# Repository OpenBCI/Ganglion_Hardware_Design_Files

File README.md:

# Ganglion_Hardware_Design_Files
General repo for Ganglion hardware files 

All design files made with KiCad PCB design software.
http://kicad.org/

Disclaimer:

These files are presented AS IS, with no representation of warranty or functionality.
Designs are subject to change without notice.

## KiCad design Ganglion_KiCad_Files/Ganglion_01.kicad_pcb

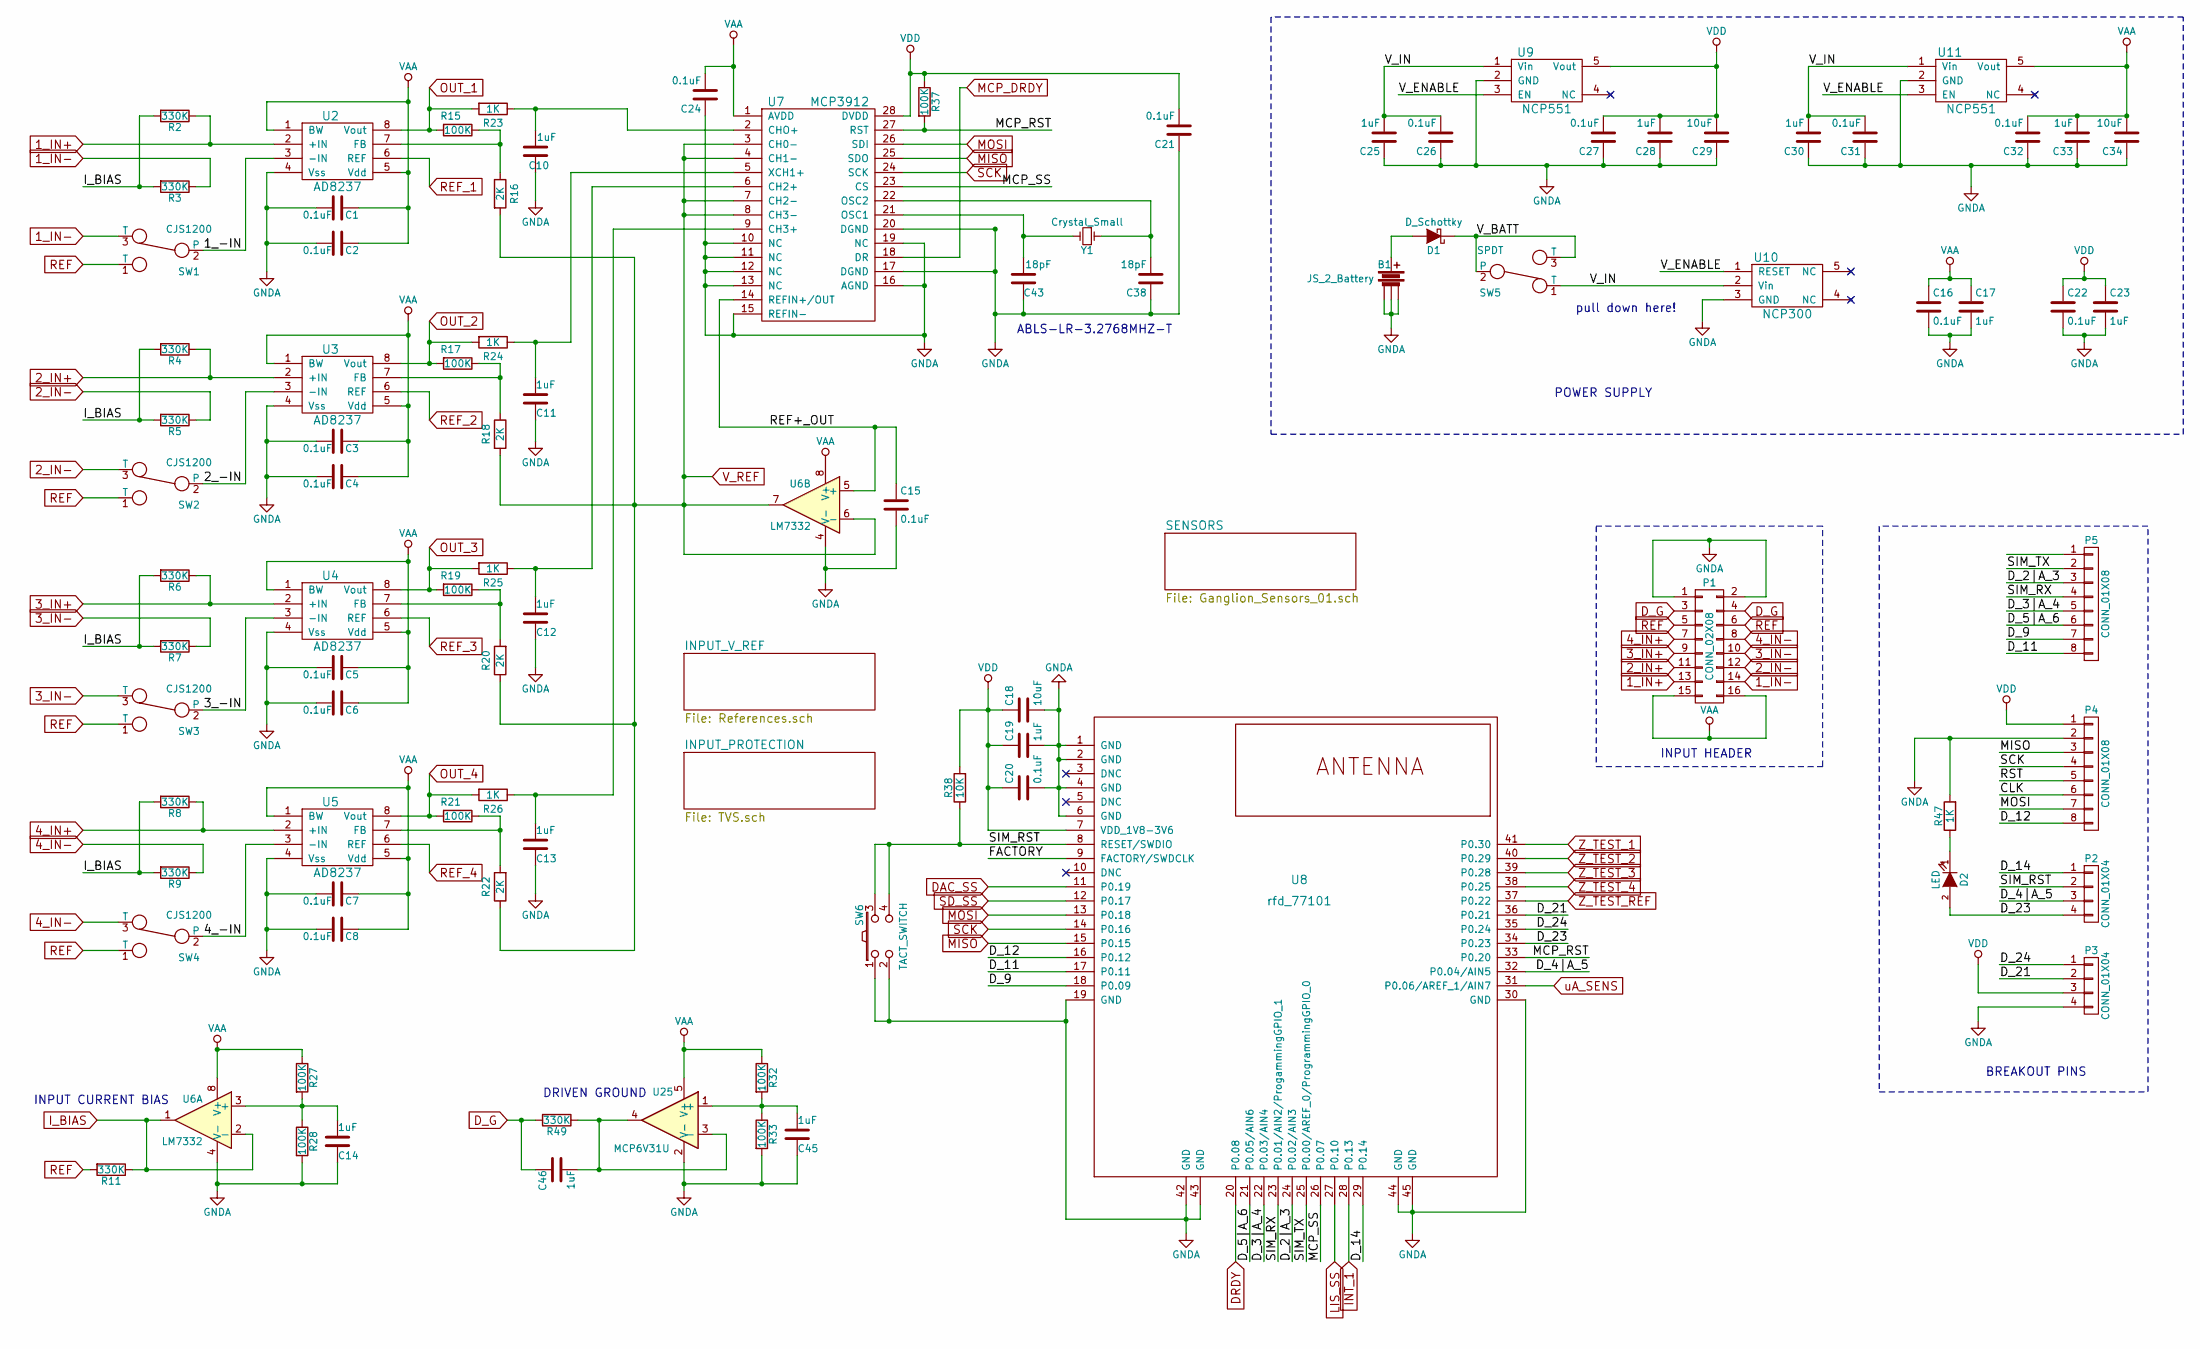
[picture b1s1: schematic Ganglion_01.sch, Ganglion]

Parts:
B1: JS_2_Battery; JST_RA_SMT; ManufacturerPartNumber S2B-PH-SM4-TB(LF)(SN)
C1, C2, C3, C4, C5, C6, C7, C8, C15, C16, C20, C21, C22, C24, C26, C27, C31, C32: 0.1uF; C_0603; ManufacturerPartNumber GRM188R71H104KA93D
C10, C11, C12, C13, C14, C17, C19, C23, C25, C28, C30, C33, C45: 1uF; C_0603; ManufacturerPartNumber GRM188R61E105KA12D
C18, C29, C34: 10uF; C_0603; ManufacturerPartNumber GRM188C80G106ME47D
C38, C43: 18pF; C_0603; ManufacturerPartNumber GRM1885C1H180JA01D
C46: 1uF; C_0603; ManufacturerPartNumber GRM188R71H104KA93D
D1: D_Schottky; C_0603; ManufacturerPartNumber CDBU0130L
D2: LED; LED_0603; ManufacturerPartNumber LTST-C193TBKT-5A
P1: CONN_02X08; Pin_Header_Angled_2x08; ManufacturerPartNumber PRPC008DBAN-M71RC
P2, P3: CONN_01X04; Socket_Strip_Straight_1x04; ManufacturerPartNumber PPTC041LFBN-RC
P4, P5: CONN_01X08; Socket_Strip_Straight_1x08; ManufacturerPartNumber PPTC081LFBN-RC
R2, R3, R4, R5, R6, R7, R8, R9, R11, R49: 330K; R_0603; ManufacturerPartNumber ERJ-3EKF3303V
R15, R17, R19, R21, R27, R28, R32, R33, R37: 100K; R_0603; ManufacturerPartNumber ERJ-3EKF1003V
R16, R18, R20, R22: 2K; R_0603; ManufacturerPartNumber ERJ-3EKF2001V
R23, R24, R25, R26, R47: 1K; R_0603; ManufacturerPartNumber ERJ-3EKF1001V
R38: 10K; R_0603; ManufacturerPartNumber ERJ-3EKF1002V
SW1, SW2, SW3, SW4: CJS1200; CJS-1200TA; ManufacturerPartNumber CJS-1200TA
SW5: SPDT; SSSS810701 SSSS810701; ManufacturerPartNumber SSSS810701
SW6: TACT_SWITCH; PTS810; ManufacturerPartNumber PTS810 SJK 250 SMTR LFS
U2, U3, U4, U5: AD8237; MSOP-8_3x3mm_Pitch0.65mm; ManufacturerPartNumber AD8237ARMZ-R7
U6: LM7332; MSOP-8_3x3mm_Pitch0.65mm; ManufacturerPartNumber MCP6L02T-E/MS
U7: MCP3912; SSOP-28_5.3x10.2mm_Pitch0.65mm; ManufacturerPartNumber MCP3912A1-E/SS
U8: rfd_77101; RFD77101; ManufacturerPartNumber RFD77101
U9, U11: NCP551; SOT-23-5; ManufacturerPartNumber NCP551SN30T1G
U10: NCP300; SOT-23-5; ManufacturerPartNumber NCP300LSN30T1G
U25: MCP6V31U; SC-70-5; ManufacturerPartNumber MCP6V31UT-E/LT
Y1: Crystal_Small; Crystal_HC49-SD_SMD; ManufacturerPartNumber ABLS-LR-3.2768MHZ-T

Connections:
1_IN+: P1.13, R2.1, U2.2 (+IN); also elsewhere on the board
1_IN-: P1.14, R3.1, SW1.3 (T); also elsewhere on the board
2_IN+: P1.11, R4.1, U3.2 (+IN); also elsewhere on the board
2_IN-: P1.12, R5.1, SW2.3 (T); also elsewhere on the board
3_IN+: P1.9, R6.1, U4.2 (+IN); also elsewhere on the board
3_IN-: P1.10, R7.1, SW3.3 (T); also elsewhere on the board
4_IN+: P1.7, R8.1, U5.2 (+IN); also elsewhere on the board
4_IN-: P1.8, R9.1, SW4.3 (T); also elsewhere on the board
/1_-IN: SW1.2, U2.3 (-IN)
/2_-IN: SW2.2, U3.3 (-IN)
/3_-IN: SW3.2, U4.3 (-IN)
/4_-IN: SW4.2, U5.3 (-IN)
/CLK: P4.6
/D_2|A_3: P5.3, U8.24 (P0.02/AIN3)
/D_3|A_4: P5.5, U8.22 (P0.03/AIN4)
/D_4|A_5: P2.3, U8.32 (P0.04/AIN5)
/D_5|A_6: P5.6, U8.21 (P0.05/AIN6)
/D_9: P5.7, U8.18 (P0.09)
/D_11: P5.8, U8.17 (P0.11)
/D_12: P4.8, U8.16 (P0.12)
/D_14: P2.1, U8.29 (P0.14)
/D_21: P3.2, U8.36 (P0.21)
/D_23: D2.2 (A), P2.4, U8.34 (P0.23)
/D_24: P3.1, U8.35 (P0.24)
/FACTORY: U8.9 (FACTORY/SWDCLK)
/MCP_RST: R37.2, U7.27 (RST), U8.33 (P0.20)
/MCP_SS: U7.23 (CS), U8.26 (P0.07)
/REF+_OUT: C15.1, U6.5 (+), U7.14 (REFIN+/OUT)
/RST: P4.5
/SIM_RST: P2.2, R38.1, SW6.3, SW6.4, U8.8 (RESET/SWDIO)
/SIM_RX: P5.4, U8.23 (P0.01/AIN2/ProgammingGPIO_1)
/SIM_TX: P5.2, U8.25 (P0.00/AREF_0/ProgrammingGPIO_0)
/V_BATT: D1.1 (K), SW5.2, SW5.3 (T)
/V_ENABLE: U9.3 (EN), U10.1 (RESET), U11.3 (EN)
/V_IN: C25.2, C26.2, C30.2, C31.2, SW5.1 (T), U9.1 (Vin), U10.2 (Vin), U11.1 (Vin)
DAC_SS: U8.11 (P0.19); also elsewhere on the board
DRDY: U8.20 (P0.08); also elsewhere on the board
D_G: C46.2, P1.3, P1.4, R49.2; also elsewhere on the board
GNDA: B1.2, B1.3, B1.4, C1.2, C2.2, C3.2, C4.2, C5.2, C6.2, C7.2, C8.2, C10.1, C11.2, C12.2, C13.2, C14.2, C15.2, C16.2, C17.2, C18.2, C19.2, C20.2, C21.1, C22.2, C23.2, C24.1, C25.1, C26.1, C27.1, C28.1, C29.1, C30.1, C31.1, C32.1, C33.1, C34.1, C38.1, C43.1, C45.2, P1.1, P1.2, P3.4, P4.2, R28.2, R33.2, R47.2, SW6.1, SW6.2, U2.4 (Vss), U3.4 (Vss), U4.4 (Vss), U5.4 (Vss), U6.4 (V-), U7.10 (NC), U7.11 (NC), U7.12 (NC), U7.13 (NC), U7.15 (REFIN-), U7.16 (AGND), U7.17 (DGND), U7.19 (NC), U7.20 (DGND), U8.1 (GND), U8.2 (GND), U8.4 (GND), U8.6 (GND), U8.19 (GND), U8.30 (GND), U8.42 (GND), U8.43 (GND), U8.44 (GND), U8.45 (GND), U9.2 (GND), U10.3 (GND), U11.2 (GND), U25.2 (V-); also elsewhere on the board
INT_1: U8.28 (P0.13); also elsewhere on the board
I_BIAS: R2.2, R3.2, R4.2, R5.2, R6.2, R7.2, R8.2, R9.2, R11.1, U6.1, U6.2 (-)
LIS_SS: U8.27 (P0.10); also elsewhere on the board
MCP_DRDY: U7.18 (DR); also elsewhere on the board
MISO: P4.3, U7.25 (SDO), U8.15 (P0.15); also elsewhere on the board
MOSI: P4.7, U7.26 (SDI), U8.13 (P0.18); also elsewhere on the board
unnamed: B1.1, D1.2 (A)
unnamed: C10.2, R23.1, U7.2 (CHO+)
unnamed: C11.1, R24.1, U7.5 (XCH1+)
unnamed: C12.1, R25.1, U7.6 (CH2+)
unnamed: C13.1, R26.1, U7.9 (CH3+)
unnamed: C14.1, R27.2, R28.1, U6.3 (+)
unnamed: C38.2, U7.22 (OSC2), Y1.1
unnamed: C43.2, U7.21 (OSC1), Y1.2
unnamed: C45.1, R32.2, R33.1, U25.1 (+)
unnamed: C46.1, R49.1, U25.3 (-), U25.4
unnamed: D2.1 (K), R47.1
unnamed: R15.1, R16.1, U2.7 (FB)
unnamed: R17.1, R18.1, U3.7 (FB)
unnamed: R19.1, R20.2, U4.7 (FB)
unnamed: R21.1, R22.2, U5.7 (FB)
OUT_1: R15.2, R23.2, U2.8 (Vout); also elsewhere on the board
OUT_2: R17.2, R24.2, U3.8 (Vout); also elsewhere on the board
OUT_3: R19.2, R25.2, U4.8 (Vout); also elsewhere on the board
OUT_4: R21.2, R26.2, U5.8 (Vout); also elsewhere on the board
REF: P1.5, P1.6, R11.2, SW1.1 (T), SW2.1 (T), SW3.1 (T), SW4.1 (T); also elsewhere on the board
REF_1: U2.6 (REF); also elsewhere on the board
REF_2: U3.6 (REF); also elsewhere on the board
REF_3: U4.6 (REF); also elsewhere on the board
REF_4: U5.6 (REF); also elsewhere on the board
SCK: P4.4, U7.24 (SCK), U8.14 (P0.16); also elsewhere on the board
SD_SS: U8.12 (P0.17); also elsewhere on the board
VAA: C1.1, C2.1, C3.1, C4.1, C5.1, C6.1, C7.1, C8.1, C16.1, C17.1, C24.2, C32.2, C33.2, C34.2, P1.15, P1.16, R27.1, R32.1, U2.1 (BW), U2.5 (Vdd), U3.1 (BW), U3.5 (Vdd), U4.1 (BW), U4.5 (Vdd), U5.1 (BW), U5.5 (Vdd), U6.8 (V+), U7.1 (AVDD), U11.5 (Vout), U25.5 (V+); also elsewhere on the board
VDD: C18.1, C19.1, C20.1, C21.2, C22.1, C23.1, C27.2, C28.2, C29.2, P3.3, P4.1, R37.1, R38.2, U7.28 (DVDD), U8.7 (VDD_1V8-3V6), U9.5 (Vout); also elsewhere on the board
V_REF: R16.2, R18.2, R20.1, R22.1, U6.6 (-), U6.7, U7.3 (CH0-), U7.4 (CH1-), U7.7 (CH2-), U7.8 (CH3-); also elsewhere on the board
Z_TEST_1: U8.41 (P0.30); also elsewhere on the board
Z_TEST_2: U8.40 (P0.29); also elsewhere on the board
Z_TEST_3: U8.39 (P0.28); also elsewhere on the board
Z_TEST_4: U8.38 (P0.25); also elsewhere on the board
Z_TEST_REF: U8.37 (P0.22); also elsewhere on the board
uA_SENS: U8.31 (P0.06/AREF_1/AIN7); also elsewhere on the board

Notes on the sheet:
POWER SUPPLY
BREAKOUT PINS
pull down here!
ABLS-LR-3.2768MHZ-T
DRIVEN GROUND
INPUT CURRENT BIAS
INPUT HEADER

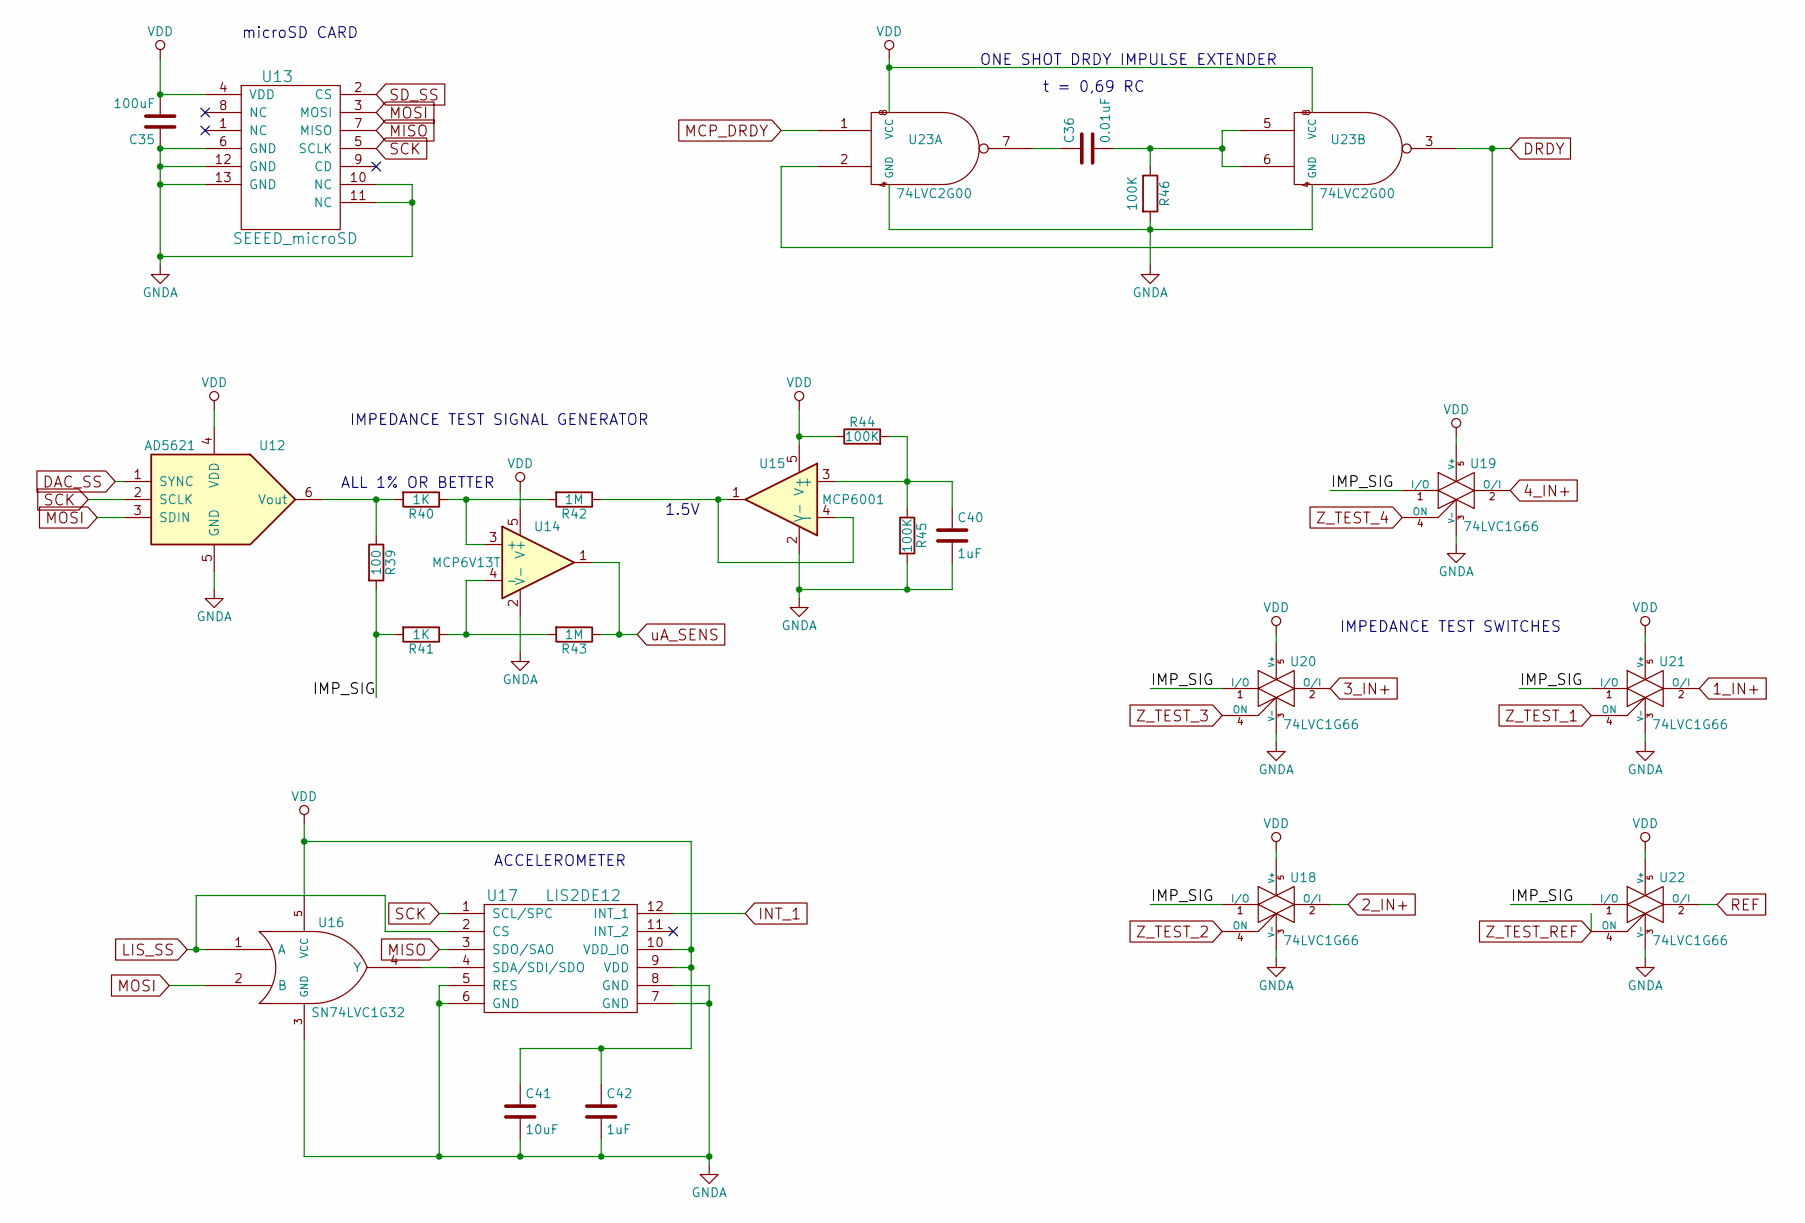
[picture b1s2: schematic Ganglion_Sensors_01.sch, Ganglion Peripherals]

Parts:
C35: 100uF; C_1210; ManufacturerPartNumber GRM21BR60J476ME15L
C36: 0.01uF; C_0603; ManufacturerPartNumber GCM188R71H103KA37D
C40, C42: 1uF; C_0603; ManufacturerPartNumber GRM188R61E105KA12D
C41: 10uF; C_0603; ManufacturerPartNumber GRM188C80G106ME47D
R39: 100; R_0603; ManufacturerPartNumber ERJ-3EKF1000V
R40, R41: 1K; R_0603; ManufacturerPartNumber ERJ-3EKF1001V
R42, R43: 1M; R_0603; ManufacturerPartNumber ERJ-3EKF1004V
R44, R45, R46: 100K; R_0603; ManufacturerPartNumber ERJ-3EKF1003V
U12: AD5621; SC-70-6; ManufacturerPartNumber AD5621AKSZ-REEL7
U13: SEEED_microSD; ST-TF-0003A; ManufacturerPartNumber ST-TF-003A
U14: MCP6V13T; SOT-23-5; ManufacturerPartNumber MCP6V31T-E/OT
U15: MCP6001; SC-70-5; ManufacturerPartNumber MCP6001T-I/LT
U16: SN74LVC1G32; SC-70-5; ManufacturerPartNumber SN74LVC1G32DCKR
U17: LIS2DE12; LIS2DH12; ManufacturerPartNumber LIS2DE12TR
U18, U19, U20, U21, U22: 74LVC1G66; SC-70-5; ManufacturerPartNumber 74LVC1G66GW,125
U23: 74LVC2G00; VSSOP-8; ManufacturerPartNumber SN74LVC2G00DCUR

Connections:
1_IN+: U21.2 (O/I); also elsewhere on the board
2_IN+: U18.2 (O/I); also elsewhere on the board
3_IN+: U20.2 (O/I); also elsewhere on the board
4_IN+: U19.2 (O/I); also elsewhere on the board
/SENSORS/IMP_SIG: R39.2, R41.2, U18.1 (I/O), U19.1 (I/O), U20.1 (I/O), U21.1 (I/O), U22.1 (I/O)
DAC_SS: U12.1 (SYNC); also elsewhere on the board
DRDY: U23.2, U23.3; also elsewhere on the board
GNDA: C35.1, C40.2, C41.2, C42.2, R45.2, R46.2, U12.5 (GND), U13.6 (GND), U13.10 (NC), U13.11 (NC), U13.12 (GND), U13.13 (GND), U14.2 (V-), U15.2 (V-), U16.3 (GND), U17.5 (RES), U17.6 (GND), U17.7 (GND), U17.8 (GND), U18.3 (V-), U19.3 (V-), U20.3 (V-), U21.3 (V-), U22.3 (V-), U23.4 (GND); also elsewhere on the board
INT_1: U17.12 (INT_1); also elsewhere on the board
LIS_SS: U16.1 (A), U17.2 (CS); also elsewhere on the board
MCP_DRDY: U23.1; also elsewhere on the board
MISO: U13.7 (MISO), U17.3 (SDO/SAO); also elsewhere on the board
MOSI: U12.3 (SDIN), U13.3 (MOSI), U16.2 (B); also elsewhere on the board
unnamed: C36.1, U23.7
unnamed: C36.2, R46.1, U23.5, U23.6
unnamed: C40.1, R44.2, R45.1, U15.3 (+)
unnamed: R39.1, R40.2, U12.6 (Vout)
unnamed: R40.1, R42.2, U14.3 (+)
unnamed: R41.1, R43.2, U14.4 (-)
unnamed: R42.1, U15.1, U15.4 (-)
unnamed: U16.4 (Y), U17.4 (SDA/SDI/SDO)
REF: U22.2 (O/I); also elsewhere on the board
SCK: U12.2 (SCLK), U13.5 (SCLK), U17.1 (SCL/SPC); also elsewhere on the board
SD_SS: U13.2 (CS); also elsewhere on the board
VDD: C35.2, C41.1, C42.1, R44.1, U12.4 (VDD), U13.4 (VDD), U14.5 (V+), U15.5 (V+), U16.5 (VCC), U17.9 (VDD), U17.10 (VDD_IO), U18.5 (V+), U19.5 (V+), U20.5 (V+), U21.5 (V+), U22.5 (V+), U23.8 (VCC); also elsewhere on the board
Z_TEST_1: U21.4 (ON); also elsewhere on the board
Z_TEST_2: U18.4 (ON); also elsewhere on the board
Z_TEST_3: U20.4 (ON); also elsewhere on the board
Z_TEST_4: U19.4 (ON); also elsewhere on the board
Z_TEST_REF: U22.4 (ON); also elsewhere on the board
uA_SENS: R43.1, U14.1; also elsewhere on the board

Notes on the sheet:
1.5V
ALL 1% OR BETTER
ACCELEROMETER
microSD CARD
IMPEDANCE TEST SIGNAL GENERATOR
ONE SHOT DRDY IMPULSE EXTENDER
t = 0,69 RC
IMPEDANCE TEST SWITCHES

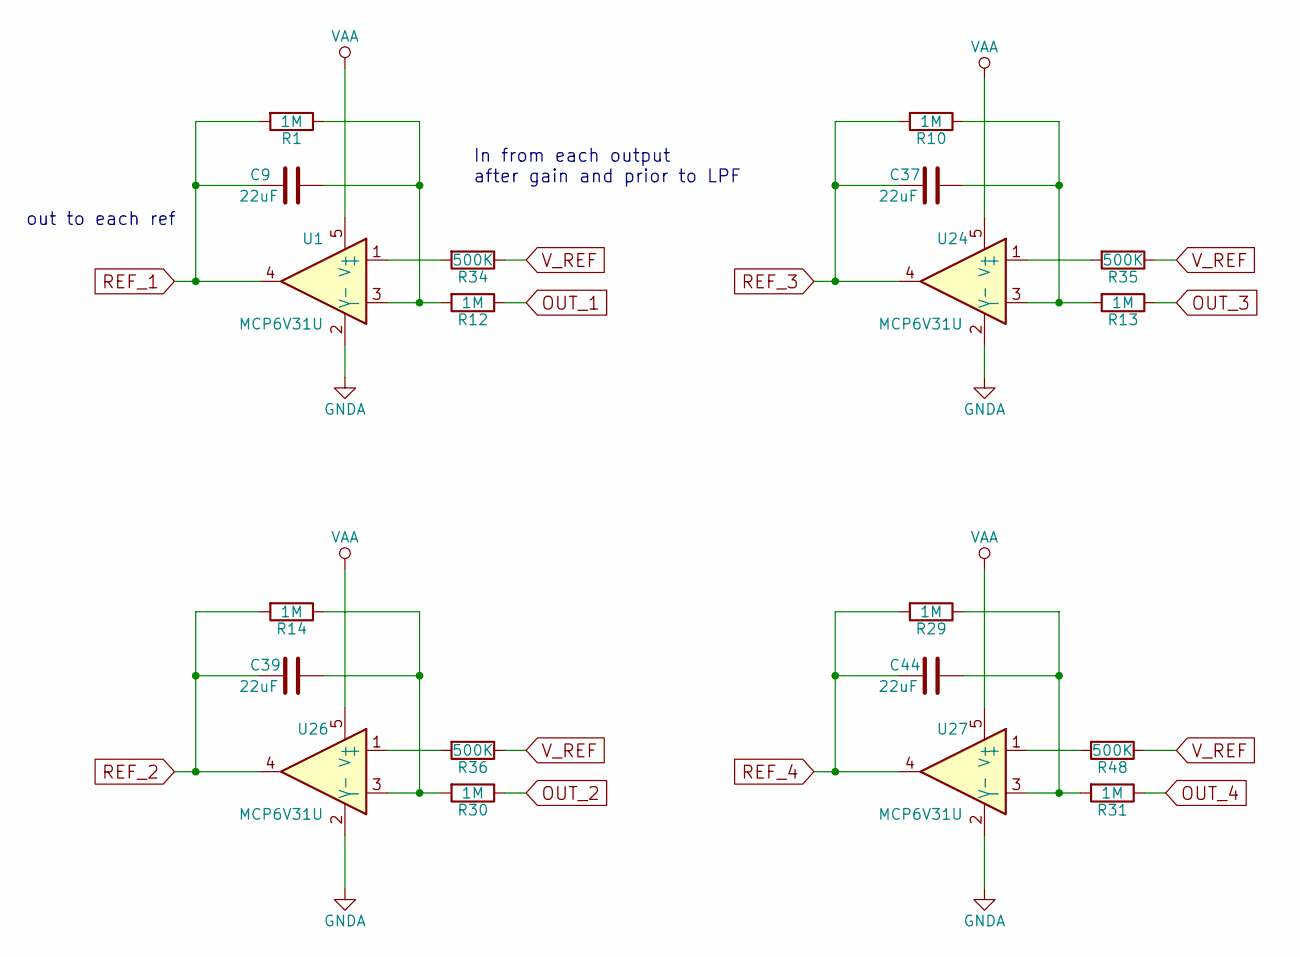
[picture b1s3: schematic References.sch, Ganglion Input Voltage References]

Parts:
C9, C37, C39, C44: 22uF; C_0603; ManufacturerPartNumber GRM188R60J226MEA0D
R1, R10, R12, R13, R14, R29, R30, R31: 1M; C_0603; ManufacturerPartNumber ERJ-3EKF1004V
R34, R35, R36, R48: 500K; C_0603; ManufacturerPartNumber CR0603-FX-4993ELF
U1, U24, U26, U27: MCP6V31U; SC-70-5; ManufacturerPartNumber MCP6V31UT-E/LT

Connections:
GNDA: U1.2 (V-), U24.2 (V-), U26.2 (V-), U27.2 (V-); also elsewhere on the board
unnamed: C9.1, R1.1, R12.2, U1.3 (-)
unnamed: C37.1, R10.1, R13.2, U24.3 (-)
unnamed: C39.1, R14.1, R30.2, U26.3 (-)
unnamed: C44.1, R29.1, R31.2, U27.3 (-)
unnamed: R34.2, U1.1 (+)
unnamed: R35.2, U24.1 (+)
unnamed: R36.2, U26.1 (+)
unnamed: R48.2, U27.1 (+)
OUT_1: R12.1; also elsewhere on the board
OUT_2: R30.1; also elsewhere on the board
OUT_3: R13.1; also elsewhere on the board
OUT_4: R31.1; also elsewhere on the board
REF_1: C9.2, R1.2, U1.4; also elsewhere on the board
REF_2: C39.2, R14.2, U26.4; also elsewhere on the board
REF_3: C37.2, R10.2, U24.4; also elsewhere on the board
REF_4: C44.2, R29.2, U27.4; also elsewhere on the board
VAA: U1.5 (V+), U24.5 (V+), U26.5 (V+), U27.5 (V+); also elsewhere on the board
V_REF: R34.1, R35.1, R36.1, R48.1; also elsewhere on the board

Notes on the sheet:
In from each output after gain and prior to LPF
out to each ref

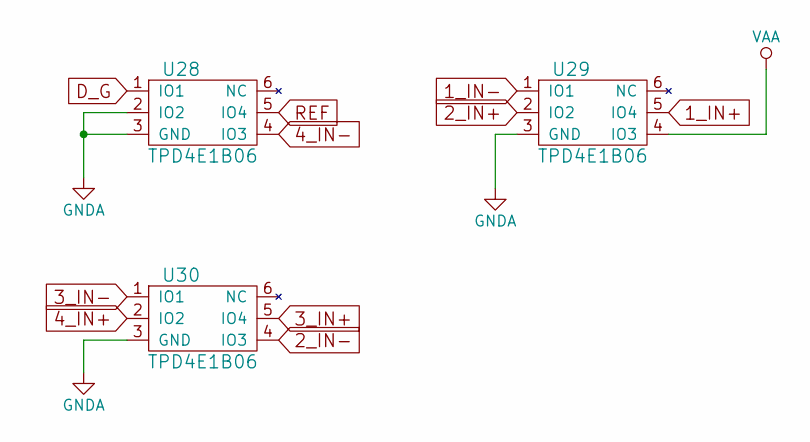
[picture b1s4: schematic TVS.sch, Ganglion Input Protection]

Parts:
U28, U29, U30: TPD4E1B06; SC-70-6; ManufacturerPartNumber TPD4E1B06DCKR

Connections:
1_IN+: U29.5 (IO4); also elsewhere on the board
1_IN-: U29.1 (IO1); also elsewhere on the board
2_IN+: U29.2 (IO2); also elsewhere on the board
2_IN-: U30.4 (IO3); also elsewhere on the board
3_IN+: U30.5 (IO4); also elsewhere on the board
3_IN-: U30.1 (IO1); also elsewhere on the board
4_IN+: U30.2 (IO2); also elsewhere on the board
4_IN-: U28.4 (IO3); also elsewhere on the board
D_G: U28.1 (IO1); also elsewhere on the board
GNDA: U28.2 (IO2), U28.3 (GND), U29.3 (GND), U30.3 (GND); also elsewhere on the board
REF: U28.5 (IO4); also elsewhere on the board
VAA: U29.4 (IO3); also elsewhere on the board

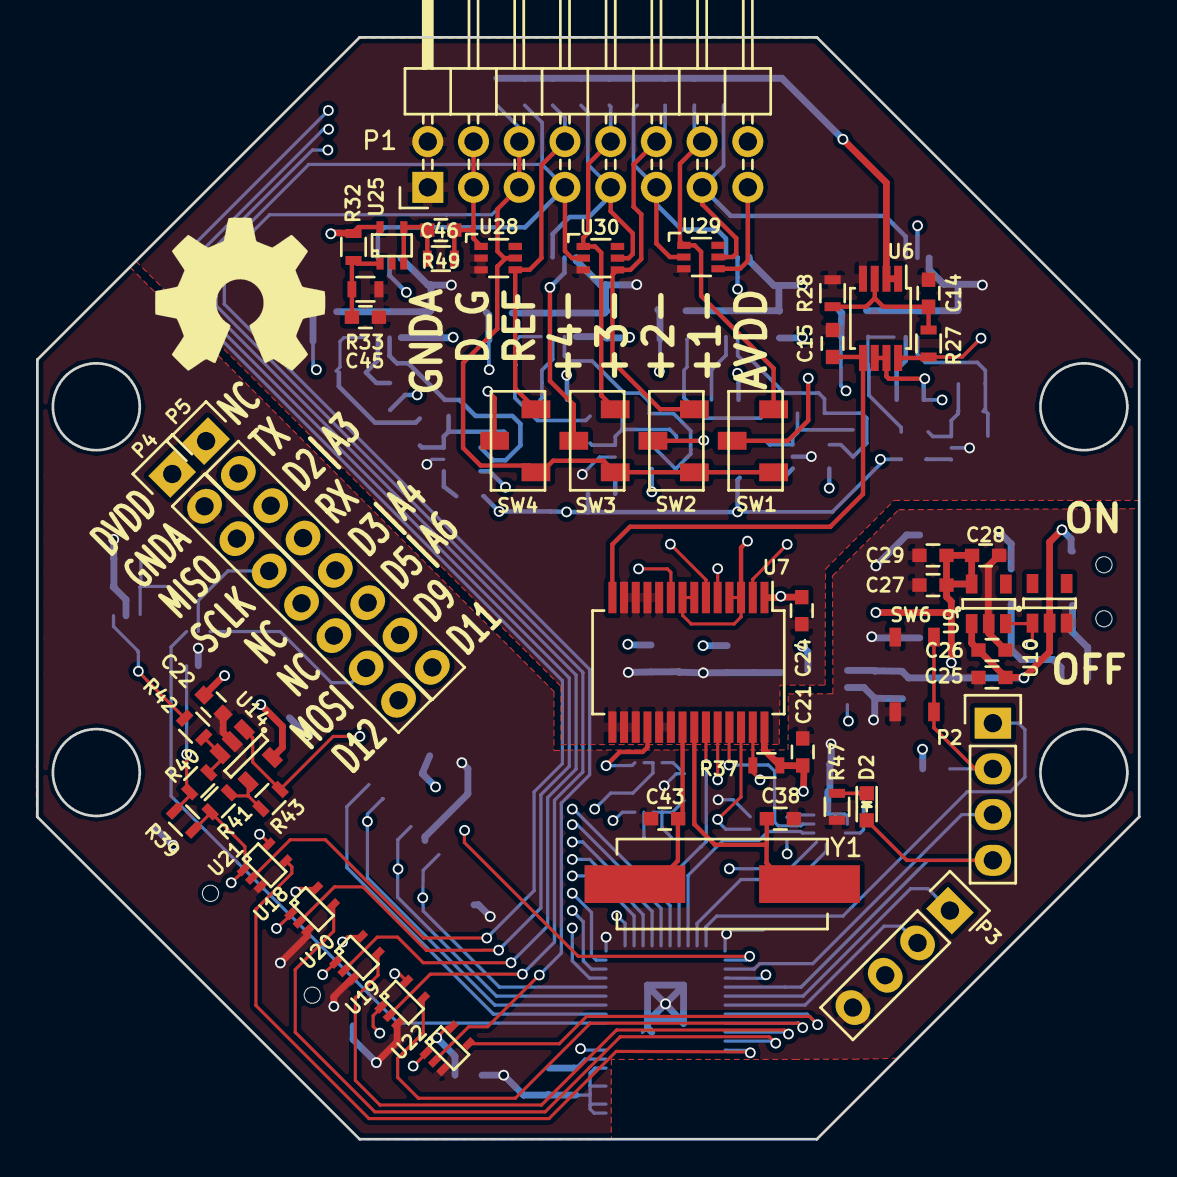
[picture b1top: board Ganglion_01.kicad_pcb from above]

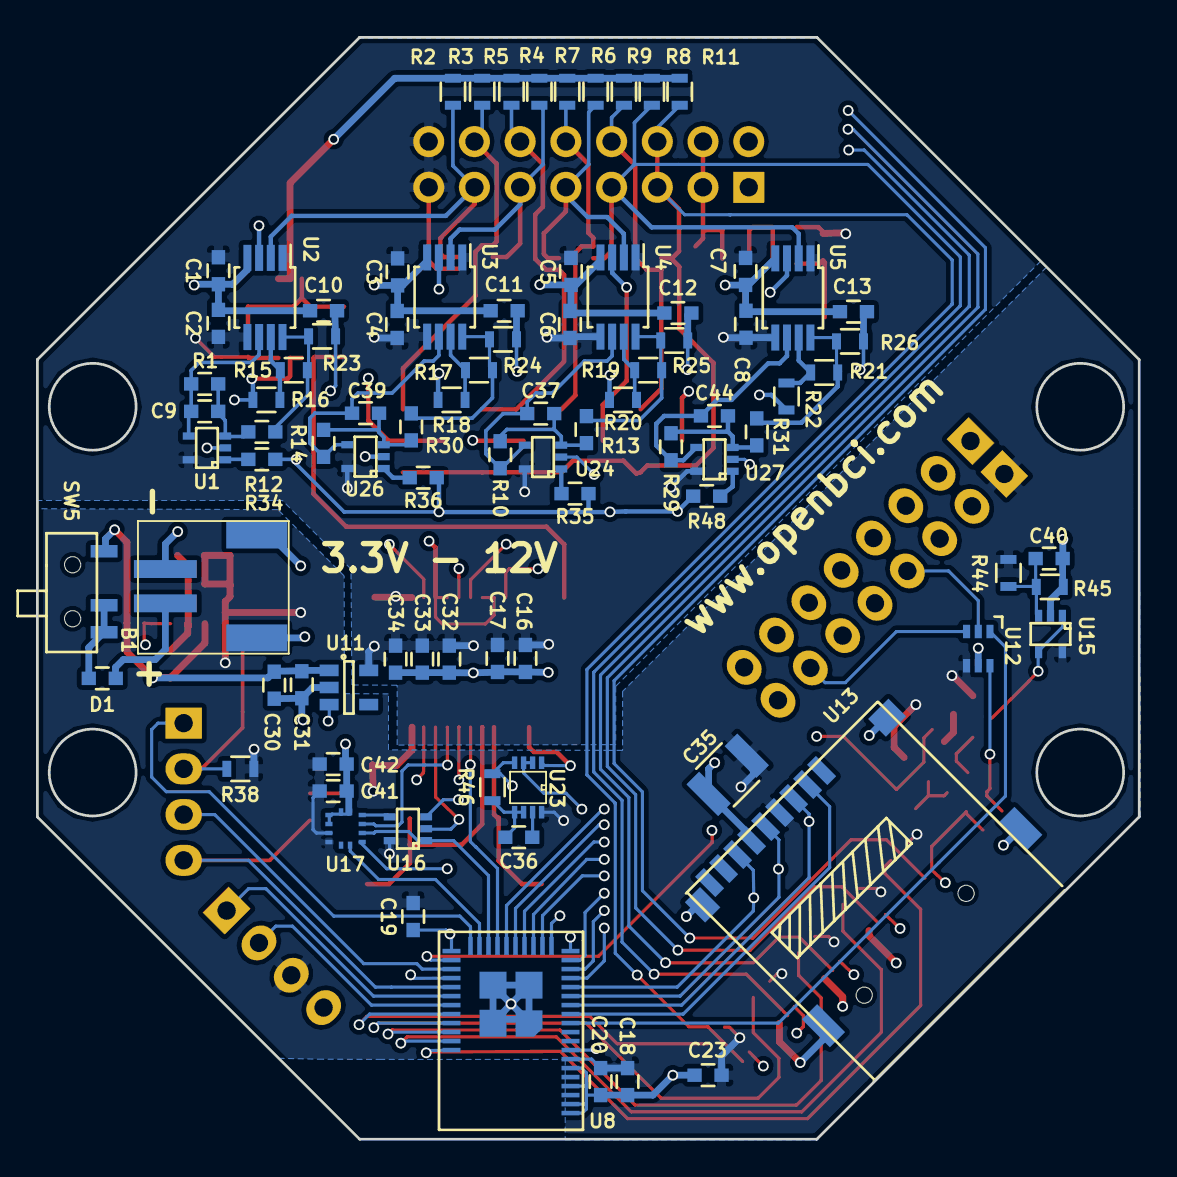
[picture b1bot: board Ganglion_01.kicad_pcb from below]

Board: 4 copper layers, 61.2 x 61.2 mm, 140 parts (88 on the bottom side), 94 nets.

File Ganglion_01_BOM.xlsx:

Item | Reference | Value | Thing | Part Number | Manufacturer | Footprint | QTY
1 | B1 | JS_2_Battery | Battery Connector | S2B-PH-SM4-TB(LF)(SN) | Various | OpenBCI:JST_RA_SMT | 1
2 | C10,C11,C12,C13,C25,C30,C33,C28,C19,C17,C23,C14,C45,C42,C40 | 1uF | C_0603 | GRM188R61E105KA12D | Murata | Capacitors_SMD:C_0603 | 15
3 | C34,C29,C18,C41 | 10uF | C_0603 | GRM188C80G106ME47D | Murata | Capacitors_SMD:C_0603 | 4
4 | C35 | 47uF | 47uF | GRM21BR60J476ME15L | Murata | Capacitors_SMD:C_1210 | 1
5 | C36 | 0.01uF | C_0603 | GCM188R71H103KA37D | Murata | Capacitors_SMD:C_0603 | 1
6 | C43,C38 | 18pF | C_0603 | GRM1885C1H180JA01D | Murata | Capacitors_SMD:C_0603 | 2
7 | C7,C5,C4,C2,C1,C3,C6,C8,C21,C24,C26,C31,C32,C27,C20,C15,C16,C22,C46 | 0.1uF | C_0603 | GRM188R71H104KA93D | Murata | Capacitors_SMD:C_0603 | 19
8 | C9,C37,C39,C44 | 22uF | C_0603 | GRM188R60J226MEA0D | Murata | Capacitors_SMD:C_0603 | 4
9 | D1 | D_Schottky | Schottkey Diode | CDBU0130L | Comchip | Capacitors_SMD:C_0603 | 1
10 | D2 | LED | Blue LED | LTST-C193TBKT-5A | Lite-On | LEDs:LED_0603 | 1
11 | P1 | CONN_02X08 | 2x8 RA Header Row | PRPC008DBAN-M71RC | Sullins | Pin_Headers:Pin_Header_Angled_2x08 | 1
12 | P2,P3 | CONN_01X04 | Socket_Strip_Straight_1x04 0.1” pitch | PPTC041LFBN-RC | Sullins | Socket_Strips:Socket_Strip_Straight_1x04 | 2
13 | P4,P5 | CONN_01X08 | Socket_Strip_Straight_1x08 0.1” pitch | PPTC081LFBN-RC | Sullins | Socket_Strips:Socket_Strip_Straight_1x08 | 2
14 | R16,R18,R20,R22 | 2K | R_0603 | ERJ-3EKF2001V | Panasonic | Resistors_SMD:R_0603 | 4
15 | R2,R3,R4,R5,R6,R7,R8,R9,R11,R49 | 330K | R_0603 | ERJ-3EKF3303V | Panasonic | Resistors_SMD:R_0603 | 10
16 | R23,R24,R25,R26,R47,R40,R41 | 1K | R_0603 | ERJ-3EKF1001V | Panasonic | Resistors_SMD:R_0603 | 7
17 | R34,R35,R48,R36 | 500K | R_0603 | CR0603-FX-4993ELF | Bourns | Capacitors_SMD:C_0603 | 4
18 | R37,R15,R17,R19,R21,R27,R28,R32,R33,R44,R45,R46 | 100K | R_0603 | ERJ-3EKF1003V | Panasonic | Resistors_SMD:R_0603 | 12
19 | R38 | 10K | Resistors_SMD: | ERJ-3EKF1002V | Panasonic | Resistors_SMD:R_0603 | 1
20 | R39 | 100R | 100R | ERJ-3EKF1000V | Panasonic | Resistors_SMD:R_0603 | 1
21 | R42,R43,R1,R12,R10,R13,R14,R30,R31,R29 | 1M | R_0603 | ERJ-3EKF1004V | Panasonic | Resistors_SMD:R_0603 | 10
22 | SW3,SW2,SW1,SW4 | CJS1200 | DIP Switch | CJS-1200TA | Copal | OpenBCI:CJS-1200TA | 4
23 | SW5 | SPDT | SPDT Power Switch | SSSS810701 | Alps | OpenBCI:SSSS810701 | 1
24 | SW6 | TACT_SWITCH | Tact Switch | PTS810 SJK 250 SMTR LFS | C&K | OpenBCI:PTS810 | 1
25 | U10 | NCP300 | Voltage Trigger | NCP300LSN30T1G | On Semi | TO_SOT_Packages_SMD:SOT-23-5 | 1
26 | U12 | AD5621 | 12bit DAC | AD5621AKSZ-REEL7 | Analog Devices | TO_SOT_Packages_SMD:SC-70-6 | 1
27 | U13 | SEEED_microSD | microSD Card | ST-TF-003A | SEEED | OpenBCI:ST-TF-0003A | 1
28 | U14 | MCP6V13T | OpAmp | MCP6V31T-E/OT | Microchip | TO_SOT_Packages_SMD:SOT-23-5 | 1
29 | U15 | MCP6001 | OpAmp | MCP6001T-I/LT | Microchip | TO_SOT_Packages_SMD:SC-70-5 | 1
30 | U16 | SN74LVC1G32 | NOR Gate | SN74LVC1G32DCKR | Texas Instrument | TO_SOT_Packages_SMD:SC-70-5 | 1
31 | U17 | LIS2DE12 | Accelerometer | LIS2DE12TR | ST Microelectronics | OpenBCI:LIS2DH12 | 1
32 | U2,U3,U4,U5 | AD8237 | InAmp | AD8237ARMZ-R7 | Analog Devices | Housings_SSOP:MSOP-8_3x3mm_Pitch0.65mm | 4
33 | U21,U19,U20,U18,U22 | 74LVC1G66 | Analog Switch IC | 74LVC1G66GW,125 | NXP | TO_SOT_Packages_SMD:SOT-353 | 5
34 | U23 | 74LVC2G00 | Dual NAND Gate | SN74LVC2G00DCUR | Texas Instrument | OpenBCI:VSSOP-8 | 1
35 | U25,U1,U24,U26,U27 | MCP6V31U | OpAmp | MCP6V31UT-E/LT | Texas Instrument | TO_SOT_Packages_SMD:SC-70-5 | 5
36 | U28,U30,U29 | TPD4E1B06 | TVS | TPD4E1B06DCKR | Texas Instrument | TO_SOT_Packages_SMD:SC-70-6 | 3
37 | U6 | LM7332 | Dual OpAmp | MCP6L02T-E/MS | Microchip | Housings_SSOP:MSOP-8_3x3mm_Pitch0.65mm | 1
38 | U7 | MCP3912 | AFE | MCP3912A1-E/SS | Microchip | Housings_SSOP:SSOP-28_5.3x10.2mm_Pitch0.65mm | 1
39 | U8 | rfd_77101 | Simblee | RFD-77101 | RF digital | OpenBCI:RFD77101 | 1
40 | U9,U11 | NCP551 | 3V Reg | NCP551SN30T1G | On Semi | TO_SOT_Packages_SMD:SOT-23-5 | 2
41 | Y1 | Xtal | 3.2768MHz | ABLS-LR-3.2768MHZ-T | Abracon | OpenBCI:ABM3C | 1

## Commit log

2016-10-18 Initial Commit
    Dropping KiCad Schematic and library files
2016-10-18 added PDF of Schematic
2016-10-19 small changes
    improved readability of shcematic
2016-10-24 small changes
2017-01-11 Commit PCB files
    Update with the production schematic and PCB files. Also the BOM.
    You’re welcome.
2017-04-10 Update README.md
    Fixed a typo.
2017-09-18 Update License and add berbers
2018-01-08 Updated Schematic to v1.0.1
    made chante to Vref Capacitors. Was 3.3uF, now 22uF
2018-08-01 Fix path to local OpenBCI library. Fixes #4.
2018-08-05 cleanup: Add .gitignore that filters out .bak and .bck files
2018-08-05 cleanup: remove redundant .bak and .bck files
2018-08-19 Annotate components with manufacturer part numbers
2018-08-22 Fix discrepancies between schematic/board values and the BOM
2023-12-18 Delete Ganglion_KiCad_Files/OpenBCI_KiCad_library_files/OpenBCI.pretty directory
    Remove KiCad pretty directory
2023-12-18 adding pretty folder to fix broken mod files
2023-12-18 added pick and place files
